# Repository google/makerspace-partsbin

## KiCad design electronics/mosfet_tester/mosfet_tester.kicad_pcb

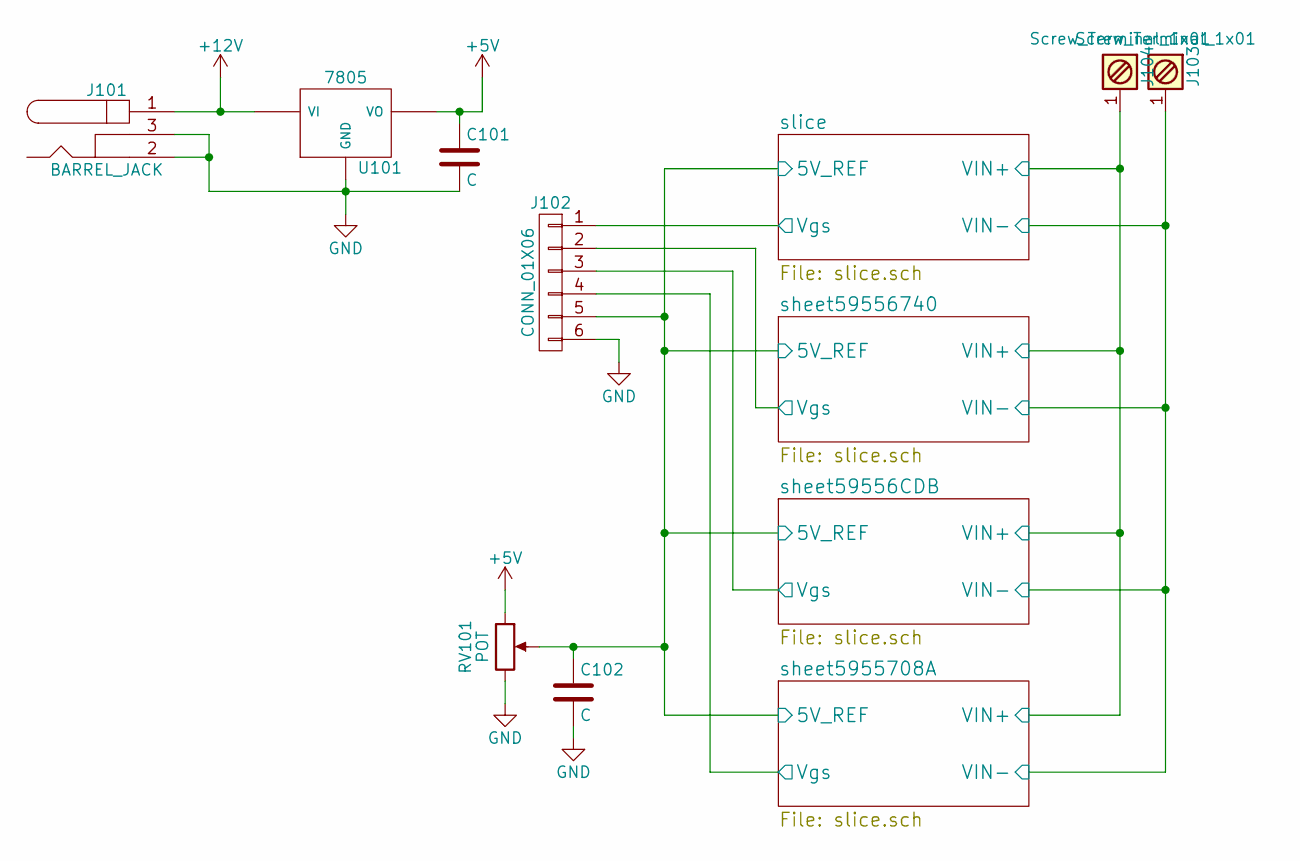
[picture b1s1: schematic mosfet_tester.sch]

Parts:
C101: C; C_1206
C102: C; C_0603
J101: BARREL_JACK
J102: CONN_01X06; Molex_KK-6410-06_06x2.54mm_Straight
J103, J104: Screw_Terminal_1x01; 4_Pin_Screw_Connector
RV101: POT
U101: 7805

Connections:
/sheet59556CDB/Vgs: J102.3; also elsewhere on the board
/sheet5955708A/Vgs: J102.4; also elsewhere on the board
/sheet59556740/5V_REF: C102.1, J102.5, RV101.2; also elsewhere on the board
/sheet59556740/VIN+: J104.1; also elsewhere on the board
/sheet59556740/VIN-: J103.1; also elsewhere on the board
/sheet59556740/Vgs: J102.2; also elsewhere on the board
/slice/Vgs: J102.1; also elsewhere on the board
GND: C101.2, C102.2, J101.2, J101.3, J102.6, RV101.3, U101.GND; also elsewhere on the board
unnamed: J101.1, U101.VI
unnamed: C101.1, RV101.1, U101.VO

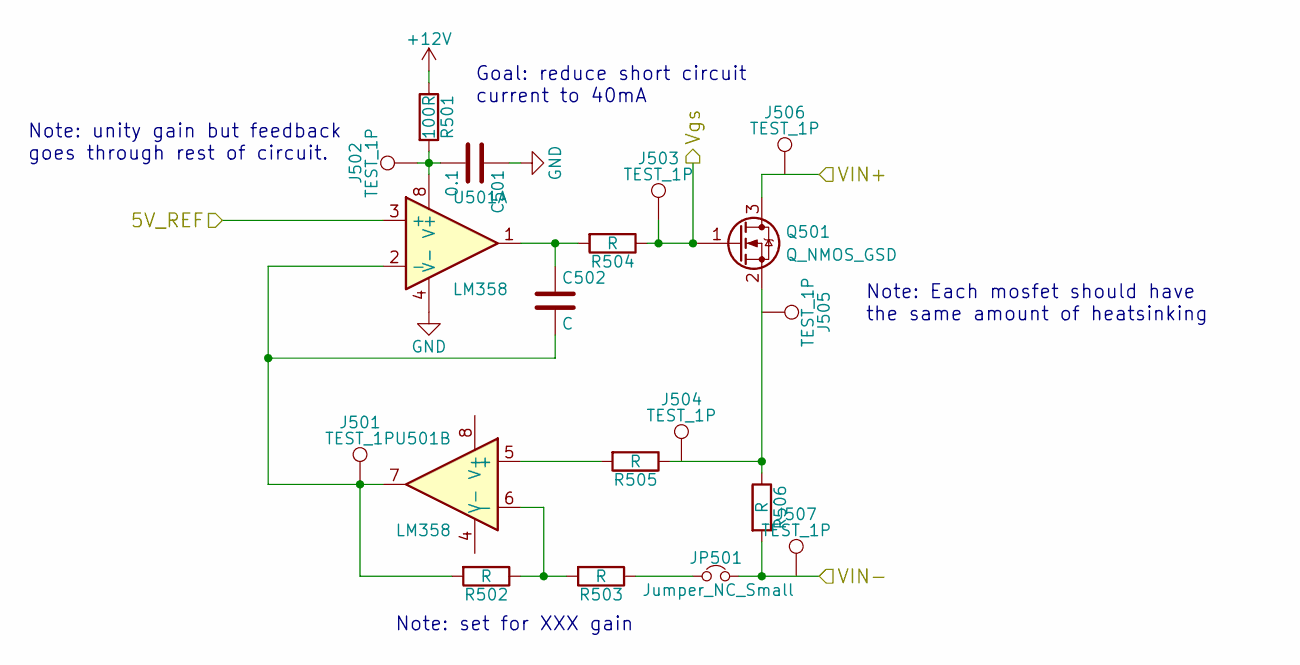
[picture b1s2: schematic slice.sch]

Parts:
C201: 0.1; C_0603
C202: C; C_0603
J201, J202, J203, J204, J205, J206, J207: TEST_1P; Pin_Header_Straight_1x01_Pitch2.54mm
JP201: Jumper_NC_Small; SJ_1_NO
Q201: Q_NMOS_GSD; SOT-23_Handsoldering
R201: 100R; R_0603_HandSoldering
R202, R203, R204, R205: R; R_0603_HandSoldering
R206: R; R_2816_HandSoldering
U201: LM358; SOIC-8_3.9x4.9mm_Pitch1.27mm

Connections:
+12V: R201.1; also elsewhere on the board
/sheet59556740/5V_REF: U201.3 (+); also elsewhere on the board
/sheet59556740/VIN+: Q201.3 (D); also elsewhere on the board
/sheet59556740/VIN-: JP201.2, R206.2; also elsewhere on the board
/slice/Vgs: J203.1, Q201.1 (G), R204.1; also elsewhere on the board
GND: C201.1, U201.4 (V-); also elsewhere on the board
unnamed: C201.2, J202.1, R201.2, U201.8 (V+)
unnamed: C202.1, R204.2, U201.1
unnamed: C202.2, J201.1, R202.2, U201.2 (-), U201.7
unnamed: JP201.1, R203.1
unnamed: Q201.2 (S), R205.1, R206.1
unnamed: R202.1, R203.2, U201.6 (-)
unnamed: R205.2, U201.5 (+)

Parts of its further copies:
C301, C401, C501: 0.1; C_0603
C302, C402, C502: C; C_0603
J301, J302, J303, J304, J305, J306, J307, J401, J402, J403, J404, J405, J406, J407, J501, J502, J503, J504, J505, J506, J507: TEST_1P; Pin_Header_Straight_1x01_Pitch2.54mm
JP301, JP401, JP501: Jumper_NC_Small; SJ_1_NO
Q301, Q401, Q501: Q_NMOS_GSD; SOT-23_Handsoldering
R301, R401, R501: 100R; R_0603_HandSoldering
R302, R303, R304, R305, R402, R403, R404, R405, R502, R503, R504, R505: R; R_0603_HandSoldering
R306, R406, R506: R; R_2816_HandSoldering
U301, U401, U501: LM358; SOIC-8_3.9x4.9mm_Pitch1.27mm

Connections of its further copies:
+12V: R301.1, R401.1, R501.1; also elsewhere on the board
/sheet59556CDB/Vgs: J403.1, Q401.1 (G), R404.1; also elsewhere on the board
/sheet5955708A/Vgs: J503.1, Q501.1 (G), R504.1; also elsewhere on the board
/sheet59556740/5V_REF: U301.3 (+), U401.3 (+), U501.3 (+); also elsewhere on the board
/sheet59556740/VIN+: Q301.3 (D), Q401.3 (D), Q501.3 (D); also elsewhere on the board
/sheet59556740/VIN-: JP301.2, JP401.2, JP501.2, R306.2, R406.2, R506.2; also elsewhere on the board
/sheet59556740/Vgs: J303.1, Q301.1 (G), R304.1; also elsewhere on the board
GND: C301.1, C401.1, C501.1, U301.4 (V-), U401.4 (V-), U501.4 (V-); also elsewhere on the board
unnamed: C301.2, J302.1, R301.2, U301.8 (V+)
unnamed: C302.1, R304.2, U301.1
unnamed: C302.2, J301.1, R302.2, U301.2 (-), U301.7
unnamed: C401.2, J402.1, R401.2, U401.8 (V+)
unnamed: C402.1, R404.2, U401.1
unnamed: C402.2, J401.1, R402.2, U401.2 (-), U401.7
unnamed: C501.2, J502.1, R501.2, U501.8 (V+)
unnamed: C502.1, R504.2, U501.1
unnamed: C502.2, J501.1, R502.2, U501.2 (-), U501.7
unnamed: JP301.1, R303.1
unnamed: JP401.1, R403.1
unnamed: JP501.1, R503.1
unnamed: Q301.2 (S), R305.1, R306.1
unnamed: Q401.2 (S), R405.1, R406.1
unnamed: Q501.2 (S), R505.1, R506.1
unnamed: R302.1, R303.2, U301.6 (-)
unnamed: R305.2, U301.5 (+)
unnamed: R402.1, R403.2, U401.6 (-)
unnamed: R405.2, U401.5 (+)
unnamed: R502.1, R503.2, U501.6 (-)
unnamed: R505.2, U501.5 (+)

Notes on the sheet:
Note: Each mosfet should have the same amount of heatsinking
Note: unity gain but feedback goes through rest of circuit.
Note: set for XXX gain
Goal: reduce short circuit current to 40mA

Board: 2 copper layers, 77 parts (0 on the bottom side), 37 nets, no tracks yet.

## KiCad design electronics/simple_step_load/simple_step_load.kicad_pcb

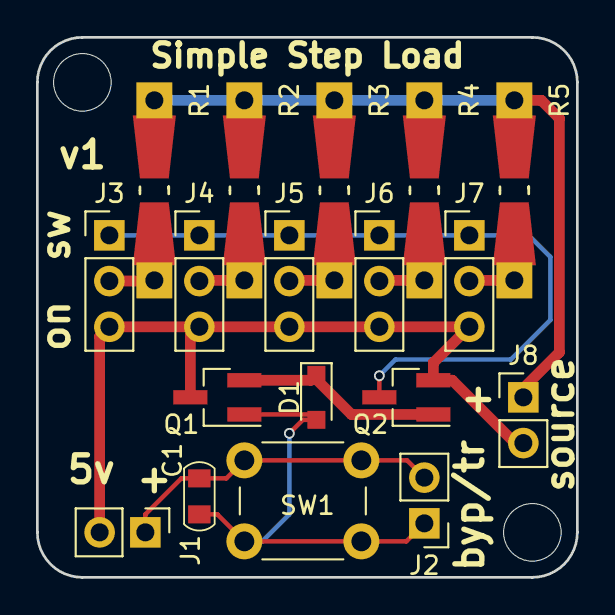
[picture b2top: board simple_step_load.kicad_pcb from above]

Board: 2 copper layers, 30.0 x 30.0 mm, 20 parts (1 on the bottom side), 11 nets.

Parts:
C1: 0.1u; C_0805
D1: D; D_SOD-323_HandSoldering
J1, J2, J8: CONN_01X02; Pin_Header_Straight_1x02_Pitch2.54mm
J3, J4, J5, J6, J7: CONN_01X03; Pin_Header_Straight_1x03_Pitch2.54mm
P1: Outline; Board_Outline_30mm_Square
P2: OSHW; OSHW-Logo2_9.8x8mm_SilkScreen
Q1: Q_PNP_BEC; SOT-23_Handsoldering
Q2: Q_NMOS_GSD; SOT-23_Handsoldering
R1, R2, R3, R4, R5: R; Resistor_SMD+THTuniversal_0805to1206_RM10_HandSoldering
SW1: SW_Push; SW_PUSH_6mm

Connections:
GND: J1.2, J3.3, J4.3, J5.3, J6.3, J7.3, J8.2, Q1.3, Q2.2
unnamed: C1.1, D1.2, J2.1, Q1.1, SW1.2
unnamed: C1.2, J1.1, J2.2, SW1.1
unnamed: D1.1, Q1.2, Q2.1
unnamed: J3.1, J4.1, J5.1, J6.1, J7.1, Q2.3
unnamed: J3.2, R1.2
unnamed: J4.2, R2.2
unnamed: J5.2, R3.2
unnamed: J6.2, R4.2
unnamed: J7.2, R5.2
VCC: J8.1, R1.1, R2.1, R3.1, R4.1, R5.1

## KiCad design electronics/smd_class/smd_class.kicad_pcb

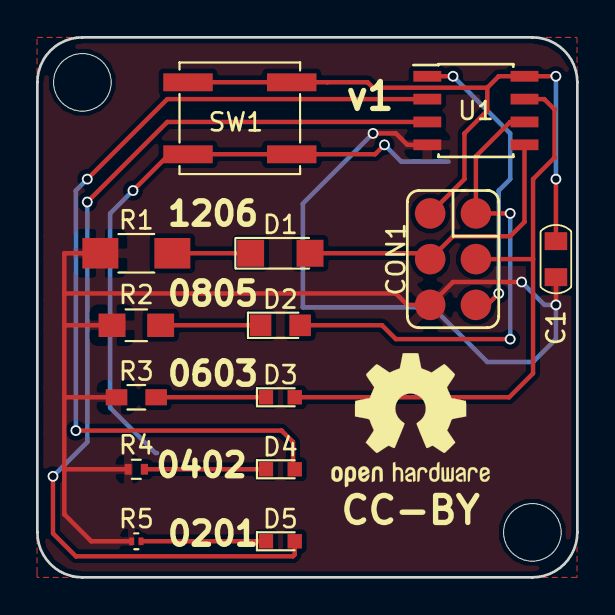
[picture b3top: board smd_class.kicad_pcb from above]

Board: 2 copper layers, 30.0 x 30.0 mm, 17 parts (1 on the bottom side), 14 nets.

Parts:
BT1: Battery_Cell; linx-bat-hld-001
C1: C; C_0805
CON1: AVR-ISP-6; Pogo_6_Doublerow
D1: LED; LED_1206
D2: LED; LED_0805
D3, D4, D5: LED; LED_0603
P1: Outline; Board_Outline_30mm_Square
P2: OSHW; OSHW-Logo2_9.8x8mm_SilkScreen
R1: 330; R_1206_HandSoldering
R2: 330; R_0805_HandSoldering
R3: 330; R_0603_HandSoldering
R4: 330; R_0402
R5: 330; R_0201
SW1: SW_Push; SW_SPST_EVQP0
U1: ATTINY85-20SU; SOIC-8_3.9x4.9mm_Pitch1.27mm

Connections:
/MISO: CON1.1, D2.2, U1.6
/MOSI: CON1.4, D1.2, U1.5
/SCK: CON1.3, D3.2, U1.7
/~RESET: CON1.5, U1.1
GND: BT1.2, C1.2, CON1.6, R1.1, R2.1, R3.1, R4.1, R5.1, U1.4
unnamed: BT1.1, SW1.1
unnamed: D1.1, R1.2
unnamed: D2.1, R2.2
unnamed: D3.1, R3.2
unnamed: D4.1, R4.2
unnamed: D4.2, U1.2
unnamed: D5.1, R5.2
unnamed: D5.2, U1.3
VCC: C1.1, CON1.2, SW1.2, U1.8

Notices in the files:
electronics/smd_class/smd_class.kicad_pcb:
CC-BY
